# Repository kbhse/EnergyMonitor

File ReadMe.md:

&nbsp;
 
* Schematic and PCB design in [KiCad](https://www.kicad.org/)

* Hardware design in [SolidWorks](https://www.solidworks.com/domain/design-engineering)

* C++ code on [PlatformIO](https://docs.platformio.org/en/latest/what-is-platformio.html) IDE

* 3D prints [Prusa i3 MK3S+](https://www.prusa3d.com)

&nbsp;

 **ESP32 based energy monitor**

Samples voltage and current waveform at 2500 Hz.
The voltage waveform is sampled from an AC/AC 9v wallplug adapter and the current waveforms with current transformers clamped round live (or neutral) conductors.

Capacity: 240v, 3 circuits up tp 95 amps each.

Intergrated into a [MQTT](https://en.wikipedia.org/wiki/MQTT) [IoT](https://en.wikipedia.org/wiki/Internet_of_things) sensor network with [Node-RED](https://nodered.org/), [InfluxDB](https://www.influxdata.com/) and [Grafana](https://grafana.com/) servers.

Uses the [EmonLib library](https://github.com/openenergymonitor/EmonLib)

[An Introduction to AC Power](https://learn.openenergymonitor.org/electricity-monitoring/ac-power-theory/introduction#an-introduction-to-ac-power)

The **ESP32** is a low-cost, low-power [system on a chip](https://en.wikipedia.org/wiki/System_on_a_chip "System on a chip") [microcontroller](https://en.wikipedia.org/wiki/Microcontroller "Microcontroller") with integrated Wi-Fi, created and developed by Espressif Systems

Specification:

- Xtensa dual-core 32-bit LX6 microprocessor
- 240 MHz
- 520 KiB SRAM, 448 KiB ROM, 16 KiB SRAM in RTC
- Ultra low power co-processor
- Wi-Fi: 802.11 b/g/n
- 34 × programmable [GPIO](https://en.wikipedia.org/wiki/General-purpose_input/output)s
- 12-bit [SAR ADC](https://en.wikipedia.org/wiki/Successive-approximation_ADC) up to 18 channels
- 2 × 8-bit [DAC](https://en.wikipedia.org/wiki/Digital-to-analog_converter)s
- 10 × touch sensors (capacitive sensing GPIOs)
- 4 × [SPI](https://en.wikipedia.org/wiki/Serial_Peripheral_Interface)
- 2 × [I²S](https://en.wikipedia.org/wiki/I%C2%B2S) interfaces
- 2 × [I²C](https://en.wikipedia.org/wiki/I%C2%B2C) interfaces
- 3 × [UART](https://en.wikipedia.org/wiki/Universal_asynchronous_receiver-transmitter)
- SD/SDIO/CE-ATA/MMC/eMMC host controller
- SDIO/SPI slave controller
- Ethernet MAC interface with dedicated DMA and IEEE 1588
- Precision Time Protocol support
- [CAN bus](https://en.wikipedia.org/wiki/CAN_bus) 2.0
- Infrared remote controller (TX/RX, up to 8 channels)
- Motor [PWM](https://en.wikipedia.org/wiki/Pulse-width_modulation)
- LED PWM (up to 16 channels)
- [Hall effect](https://en.wikipedia.org/wiki/Hall_effect) sensor
- Ultra low power analog pre-amplifier
- IEEE 802.11 standard security features all supported, including [WPA](https://en.wikipedia.org/wiki/Wi-Fi_Protected_Access), - [WPA2](https://en.wikipedia.org/wiki/Wi-Fi_Protected_Access), [WPA3](https://en.wikipedia.org/wiki/Wi-Fi_Protected_Access) and [WAPI](https://en.wikipedia.org/wiki/WLAN_Authentication_and_Privacy_Infrastructure)
- [Secure boot](https://docs.espressif.com/projects/esp-idf/en/latest/esp32/security/secure-boot-v1.html)
- [Flash encryption](https://docs.espressif.com/projects/esp-idf/en/latest/esp32/security/flash-encryption.html)
- 1024-bit [OTP](https://en.wikipedia.org/wiki/One-time_password)
- Cryptographic hardware acceleration: [AES](https://en.wikipedia.org/wiki/Advanced_Encryption_Standard), [SHA-2](https://en.wikipedia.org/wiki/SHA-2), [RSA](https://en.wikipedia.org/wiki/RSA_(cryptosystem)), [elliptic curve cryptography (ECC)](https://en.wikipedia.org/wiki/Elliptic-curve_cryptography), [random number generator (RNG)](https://en.wikipedia.org/wiki/Random_number_generation)
- Internal [low-dropout regulator](https://en.wikipedia.org/wiki/Low-dropout_regulator)
- Individual power domain for [RTC](https://en.wikipedia.org/wiki/Real-time_clock)
- 5 μA deep sleep current
- Wake up from GPIO interrupt, timer, ADC measurements, capacitive touch sensor interrupt

&nbsp;

**PCB:**

- CAD: [KiCad](https://www.kicad.org/)
- Production: [JLCPCB](https://jlcpcb.com/)

board

GndA

Gnd

[JLCPCB](https://jlcpcb.com/)

&nbsp;

**Case design** (WIP):

CAD: [SolidWorks](https://www.solidworks.com/domain/design-engineering)

Slicer: [PrusaSlicer](https://www.prusa3d.com/prusaslicer/)

Printer: [Prusa i3 MK3S+](https://www.prusa3d.com)

- Material: E-DA [PLA](https://en.wikipedia.org/wiki/Polylactic_acid)
- Nozzle: 0.4mm
- Layer Height: 0.2mm
- Infill: 20% cubic
- Support: optional
- Filament: 21m, 63g
- Print Time: 5hr 48m

Dimensions (LxWxH): 110x58x35 mm

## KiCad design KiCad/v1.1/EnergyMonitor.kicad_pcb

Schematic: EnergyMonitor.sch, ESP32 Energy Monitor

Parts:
C1: 47uF; CP_Elec_6.3x5.9
C2, C6, C7, C8, C10: 10uF; C_1206_3216Metric
C3, C4, C5: 0.1uF; C_0805_2012Metric
C9: 1uF 25V; C_0805_2012Metric
C11: 10uF; CP_Elec_6.3x5.9
D1: IN4148; D_DO-35_SOD27_P7.62mm_Horizontal
D2, D3, D4, D5: ESD5Z3.3T1G; D_SOD-523
D6: LED; LED_0805_2012Metric
H1, H2, H3, H4: MountingHole; MountingHole_2.2mm_M2_Pad_Via
J1, J2, J3, J4, J5, J6, J15: Conn_01x04; PinHeader_1x04_P2.54mm_Vertical
J7, J11: Conn_01x02; PinHeader_1x02_P2.54mm_Vertical
J8, J9, J10: AudioJack3_Ground_Switch_5_pin; 3.5mm_5_Pin_Socket_PCB_Mount
J12: Conn_01x04; JST_SH_SM04B-SRSS-TB_1x04-1MP_P1.00mm_Horizontal
J13: Barrel_Jack_Switch; DC_Barrel_Jack_Socket
J14: Conn_01x04; JST_SH_BM04B-SRSS-TB_1x04-1MP_P1.00mm_Vertical
J16: 4P4C; RJ6_4P4C_small_I2C_UM10204
J17: Conn_01x06; PinHeader_1x06_P2.54mm_Vertical
R1: 56R 0.25W; R_1206_3216Metric
R2, R6, R10: 22R; R_1206_3216Metric
R3, R7, R11: 39R; R_1206_3216Metric
R4, R8, R12: 62R; R_1206_3216Metric
R5, R9, R13: 120R; R_1206_3216Metric
R14: 4K7; R_0805_2012Metric
R15, R30, R31, R32, R33, R34: 0R; R_0805_2012Metric
R16, R17, R18: 1K; R_0805_2012Metric
R19, R20, R21, R22, R23, R24, R26, R28, R29: 470K; R_0805_2012Metric
R25: 120K; R_0805_2012Metric
R27: 10K; R_0805_2012Metric
TP1, TP2, TP3, TP4, TP5: TestPoint_Probe; TestPoint_Loop_D2.50mm_Drill1.0mm_LowProfile
U1: ESP32_D1_MINI
U2: HT7333; SOT-89-3

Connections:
9V_AC: C9.2, J11.1, J13.1
+3V3: J7.2, J12.1, J14.1, J15.3, J16.3, J17.6, R14.1, R19.1, R21.1, R23.1, R28.1, U1.16 (3V3)
ADC1_CH4: D5.1 (K), R26.1, TP4.1, U1.7 (IO35)
ADC1_CH5: D2.1 (K), R16.1, TP1.1, U1.33 (IO32)
ADC1_CH6: D3.1 (K), R17.1, TP2.1, U1.11 (IO34)
ADC1_CH7: D4.1 (K), R18.1, TP3.1, U1.9 (IO33)
GND: C1.2, C2.2, C11.2, D2.2 (A), D3.2 (A), D4.2 (A), D5.2 (A), D6.1 (K), J12.4, J13.2, J13.3, J14.4, J15.2, J16.2, J17.1, R15.1, R30.1, R31.1, R32.1, R33.1, R34.1, TP5.1, U1.1 (GND), U1.28 (GND), U1.39 (GND), U2.1 (GND)
GNDA: C6.2, C7.2, C8.2, C10.2, J8.S, J8.TN, J9.S, J9.TN, J10.S, J10.TN, R15.2, R20.2, R22.2, R24.2, R29.2, R30.2, R31.2, R32.2, R33.2, R34.2
I2C_SCL: J12.2, J14.2, J15.1, J16.1, U1.36 (IO22)
I2C_SDA: J12.3, J14.3, J15.4, J16.4, U1.34 (IO21)
unnamed: C1.1, R1.1, U2.2 (VI)
unnamed: C9.1, R25.1
unnamed: C10.1, R27.2, R28.2, R29.1
unnamed: C2.1, C11.1, J7.1, U2.3 (VO)
unnamed: D1.1 (K), R1.2
unnamed: D1.2 (A), J11.2
unnamed: D6.2 (A), R14.2
unnamed: J4.1, R5.2
unnamed: J4.2, R4.2
unnamed: J4.3, R3.2
unnamed: J4.4, R2.2
unnamed: J5.1, R9.2
unnamed: J5.2, R8.2
unnamed: J5.3, R7.2
unnamed: J5.4, R6.2
unnamed: J6.1, R13.2
unnamed: J6.2, R12.2
unnamed: J6.3, R11.2
unnamed: J6.4, R10.2
unnamed: R25.2, R26.2, R27.1
RB1: C3.1, J1.1, J1.2, J1.3, J1.4, J9.R, R16.2
RB2: C4.1, J2.1, J2.2, J2.3, J2.4, J8.R, R17.2
RB3: C5.1, J3.1, J3.2, J3.3, J3.4, J10.R, R18.2
SPI_CLK: J17.3, U1.8 (IO18)
SPI_CS: J17.5, U1.14 (IO5)
SPI_MISO: J17.2, U1.10 (IO19)
SPI_MOSI: J17.4, U1.12 (IO23)
TB1: C3.2, C6.1, J9.T, R2.1, R3.1, R4.1, R5.1, R19.2, R20.1
TB2: C4.2, C7.1, J8.T, R6.1, R7.1, R8.1, R9.1, R21.2, R22.1
TB3: C5.2, C8.1, J10.T, R10.1, R11.1, R12.1, R13.1, R23.2, R24.1

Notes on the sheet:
Current Transformer YHDC SCT-013-00 CT
tip: white ring: red sleeve: shield
nb rewire CT Sensor Jack plug disconnect red signal wire from cable shield and connect to ring.
AC-AC 9V VRMS Sample
Current Sensors
https://www.casler.org/wordpress/low-current-measurement-performance-of-the-sct013/ https://github.com/openenergymonitor/emontx3/blob/master/hardware/schematic.png https://github.com/openenergymonitor/emonpi/blob/master/hardware/emonpi/emonpi_V1_6/emonPi_V1.6_sch.png
3V3 LDO 250mA
Jumper
AC-DC Power
check these values !!
Remove Jumper if ESP32 powered by USB.
Burden resistance 11R - 23kW Max @ 240V 60R - 4kW Max @ 240V
I2C
https://www.nxp.com/docs/en/user-guide/UM10204.pdf
https://wiki.openenergymonitor.org/index.php/EmonTx_V3#Burden_Resistor_Calculations
a switched jack is utilized to provide a clear indication if a CT is connected or not. When a 3.5mm plug is NOT inserted pin 4 is connected to pin 5 which is connected to GND so when no CT is connected, the ADC will sense 0V. When a 3.5mm plug is inserted, the connection between pins 4 & 5 is broke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
burden resistors
Wemos I2C wiring
UM10204 I2C wiring
Check Wemos I2C pinout !
Should RN be connected to ground?
trace width for burden circuits
red superbright LED 0805 SMD green band -ve 1k R => 1.4mA 4K7 => 0.3mA @3.3v
Connector_JST:JST_SH_BM04B-SRSS-TB_1x04-1MP_P1.00mm_Vertical
GPIO/SPI
H7333 Input voltage 12V absolute maximum 14V
Test this !!!
provision for electrolytic output capacitor?
GPIO source 40mA sink 28mA total 1.5A

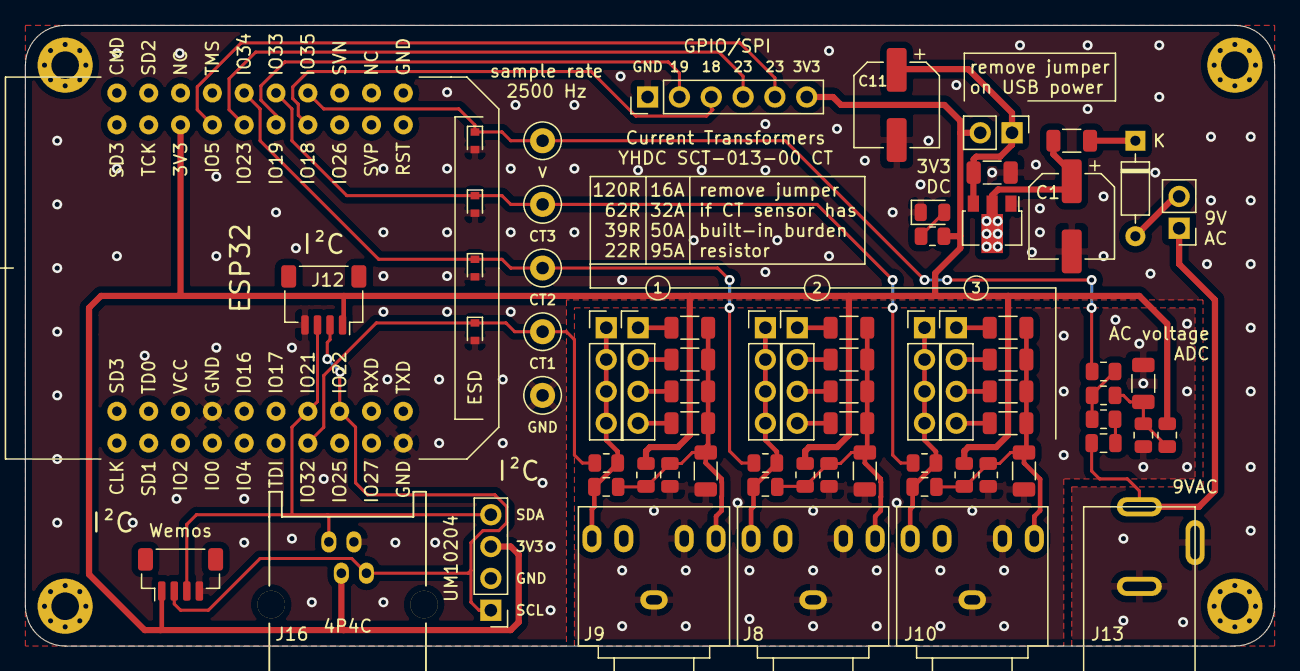
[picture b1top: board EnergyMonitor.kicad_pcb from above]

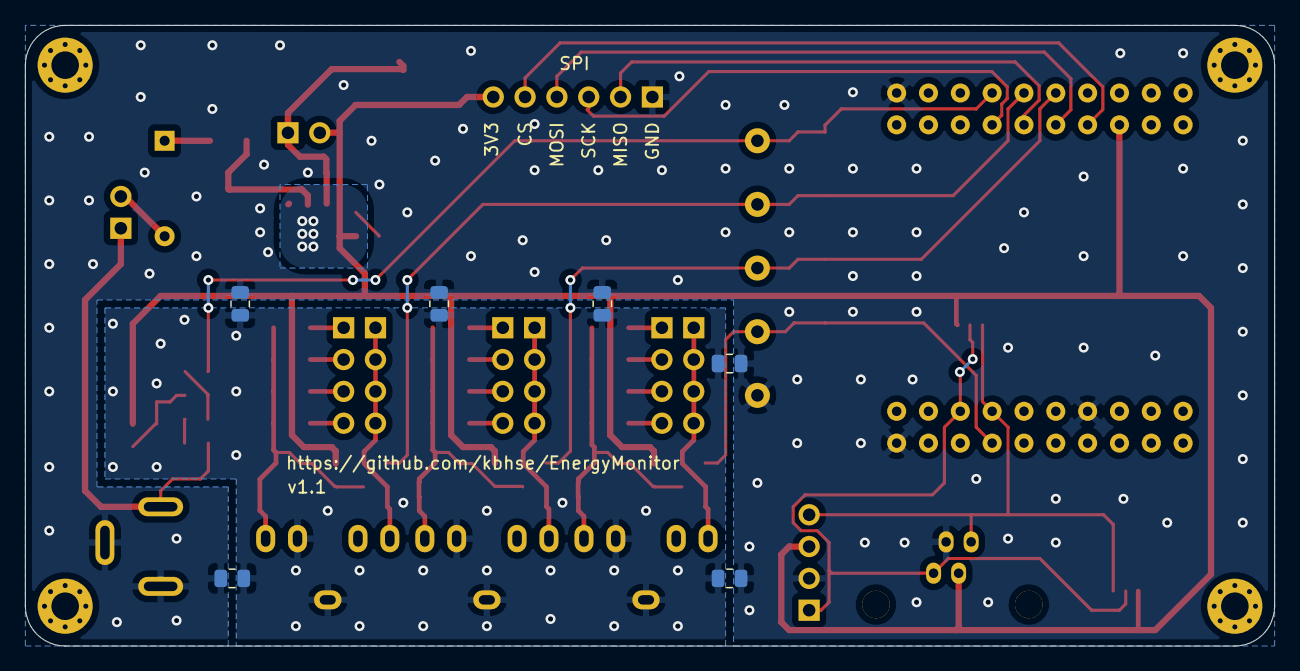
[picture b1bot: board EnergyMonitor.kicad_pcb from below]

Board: 2 copper layers, 99.7 x 49.5 mm, 79 parts (6 on the bottom side), 40 nets.

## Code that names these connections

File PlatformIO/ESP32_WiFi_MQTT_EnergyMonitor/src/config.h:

/* config.h */

#ifndef CONFIG_H   /* include guards */
#define CONFIG_H

    #include <Arduino.h>
    #include "credentials.h"

    #define PROGNAM "ESP32_WiFi_MQTT_ENERGYMONITOR"                                                     // program name
    #define VERSION "v0.12.2"                                                                           // program version (nb lowercase 'version' is keyword)
    #define PGMFUNCT ""                                                                                 // what the program does
    #define AUTHOR "klomar"                                                                             // created by
    #define CREATION_DATE "17 August 2021"                                                              // date
    #define MODIFIED_DATE "7 October 2021"
    #define DEBUG_OUT


    // ------------------------------------------------------------------
    // 

    #define CT1_PIN 32                              // the GPIO pin where CT sensor 1 is connected (ADC1_CH5)
    #define CT2_PIN 34                              // the GPIO pin where CT sensor 2 is connected (ADC1_CH6)
    #define CT3_PIN 33                              // the GPIO pin where CT sensor 3 is connected (ADC1_CH7)
    #define ACV_PIN 35                              // the GPIO pin where ACvoltage is connected (ADC1_CH4)

    //#define ADC_INPUT 34                            // the GPIO pin where the CT sensor is connected
    #define HOME_VOLTAGE 243                        // the house voltage
    #define CALIBRATION 34                          // the calibration number for the SCT-013-030 Current sensor
                                                    // 1800 turns / 62 ohms = 29.03
                                                    // 34 from calibration with plug in meter and heater @ 867 watts
                                                    // and toaster (resistive load) @ 1.2kw
                                                    // void EnergyMonitor::current(unsigned int _inPinI, double _ICAL)
                                                    // double _ICAL so floating point
                                                    // EmonLib returns 11.25 watts at 0 load
    #define ADC_BITS    10                          // Force EmonLib to use 10bit ADC resolution
    #define ADC_COUNTS  (1<<ADC_BITS)


    boolean CT1, CT2, CT3, CT4, ACAC;                // flags

    uint8_t Vrms = 240;                             // Vrms for apparent power readings (when no AC-AC voltage sample is present)
    
    // ------------------------------------------------------------------
    // Calibrations

    const float Ical1=                34;                 // (2000 turns / 22 Ohm burden) = 90.9
    const float Ical2=                34;                 // (2000 turns / 22 Ohm burden) = 90.9
    const float Ical3=                34;                 // (2000 turns / 22 Ohm burden) = 90.9

    float Vcal=                       268.97;               // (230V x 13) / (9V x 1.2) = 276.9 Calibration for UK AC-AC adapter 77DB-06-09

    const float phase_shift=          1.7;

    const int no_of_samples=          1662;
    const int no_of_half_wavelengths= 30;
    const int timeout=                2000;                               //emonLib timeout
    const int ACAC_DETECTION_LEVEL=   3000;

    //const byte LEDpin=                 6;


    /*
    typedef struct currentTransformer
        {
        int id;
        String partNo;
        int turnsRatio;
        // calibration numbers
        float burden22Cal;             // 22 ohmn burden resistor
        float burden39Cal;             // 39 ohmn burden resistor
        float burden62Cal;             // 62 ohmn burden resistor
        float burden120Cal;            // 120 ohmn burden resistor
        } CT1, CT2, CT3;
    
    currentTransformer CT1, CT2, CT3;

    CT1.burden22Cal = 90.9;             // turnsRatio / burden resistance
    */


    // ------------------------------------------------------------------

    const int onboardLED = 2;                           // GPIO2 (blue LED)
    //long MQTTupdateFreq = 10000;                      // 1 minute (the update frequency to publish data to MQTT (milliseconds))
    //#define UPDATE_FREQ 60000L                        // 60 seconds

    // ------------------------------------------------------------------
    // MCU Hardware

    //#define MCU "ESP8266 D1 Mini"
    //#define MCU "ESP8266 D1 Mini Pro V2"
    #define MCU "ESP32 Dev board"
    //#define MCU "ESP32 D1 Mini"

    // ------------------------------------------------------------------
    // Configure MQTT
    // (unique identity for each ESP32 device)

        #define MQTT_DEVICE "esp035"                                                                       // MQTT requires unique device ID (see reconnect() function)
        #define PUB_SUB_CLIENT esp035client                                                                // and unique client ?
        #define MQTT_LOCATION "esp035pcb"                                                                  // location for MQTT topic

    // ------------------------------------------------------------------
    // Comment out sensors not in use

        //#define WEMOS_SHT30 "SHT30 "                                                                              // Wemos Temperature and Humidity shield
        //#define WEMOS_HP303 "HP303 "                                                                              // Wemos Barometric Pressure Shield
        //#define WEMOS_BH1750 "BH1750 "                                                                            // Wemos Ambient Light Shield
        //#define WEMOS_BATTERY "BATTERY "                                                                          // Wemos Battery Shield
        //#define WIFI_RSSI "RSSI "                                                                                 // ESP8266 WiFi RSSI
        //#define RS485_WIND "WIND "                                                                                // Anemometer and Wind Direction
        //#define CO2 "CO2 "                                                                                        // sandbox electronics CO2 sensor - NB recalibrate in fresh air regularly
        //#define ROBOTDYN_ACDIMMER "ACDIMMER "                                                                     // Robotdyn zero-crossing detector and AC dimmer module
        //#define MLX90614_IR_SENSOR "IR "                                                                          // IR temp sensor
        //#define DS18B20 "DS18B20"                                                                                 // 1-wire temperature sensor
        #define CURRENT_SENSOR                                                                                      // YHDC SCT-013 CT Sensor
        //#define ADC_TEST                                                                                          // test

/*
    // ------------------------------------------------------------------------------------------------
    // TFT pins - see README.md

        #define TFT_CS D0  //for D1 mini or TFT I2C Connector Shield (V1.1.0 or later)
        #define TFT_DC D8  //for D1 mini or TFT I2C Connector Shield (V1.1.0 or later)
        #define TFT_RST -1 //for D1 mini or TFT I2C Connector Shield (V1.1.0 or later)
        #define TS_CS D3   //for D1 mini or TFT I2C Connector Shield (V1.1.0 or later)

*/
   
#endif // CONFIG_H

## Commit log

2021-09-04 v1.0
2021-09-04 fix url
2021-09-04 created symbol for ESP32_D1_MINI
2021-09-04 edit symbol for ESP32_D1_MINI
2021-09-04 directory structure
2021-09-05 added PlatformIO
2021-09-05 updated schematic
2021-09-05 footprint for ESP32_D1_MINI
2021-09-05 edit ESP32_D1_MINI Symbol
2021-09-06 Circuit design - schematic
2021-09-06 add ReadMe.md
2021-09-06 add image
2021-09-06 Cicruit design - schematic
2021-09-07 pcb footprints
2021-09-08 pcb layout
2021-09-09 v0.12.1
2021-09-21 circuit design & pcb layout
2021-09-21 rename images
2021-09-22 create 3D models for PCB components
2021-09-25 added 2nd I2C port
2021-09-25 added GPIO/SPI port
2021-09-25 created Gerber and Drill files
2021-09-25 fabrication gerbers v1.0
2021-09-25 v1.0 pcb in production
2021-09-27 create v1.1 schematic and pcb. case design. add thermal relief to HT7333 on v1.1 pcb
2021-09-27 v1.0 Case Design
2021-10-03 pcb fabrication and assembly, case design
2021-10-03 create firmware development branch
2021-10-03 refactoring firmware for v1.0 pcb: 3 CT sensors and vrms, I2C port and status LED
2021-10-03 v1.1 post-production fixes
2021-10-03 refactoring firmware for v1.0 pcb
2021-10-08 refactoring for 3 CT sensors
2021-10-08 refactor code for multiple CT sensors and Vrms
